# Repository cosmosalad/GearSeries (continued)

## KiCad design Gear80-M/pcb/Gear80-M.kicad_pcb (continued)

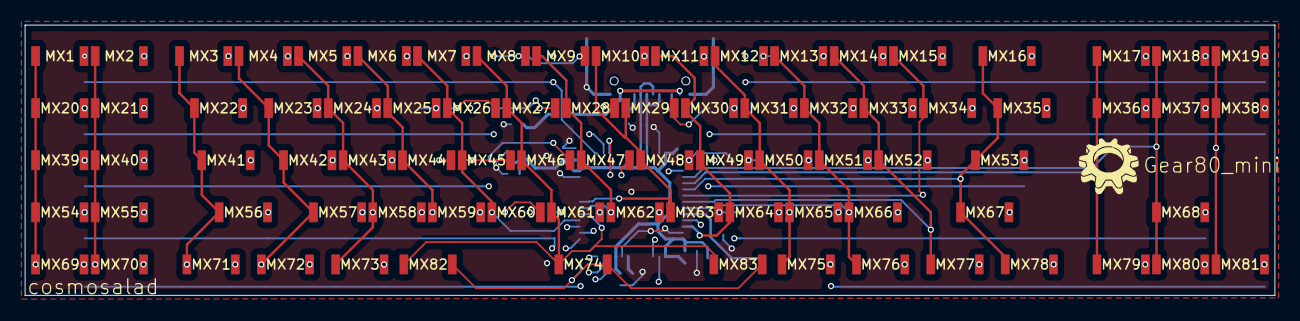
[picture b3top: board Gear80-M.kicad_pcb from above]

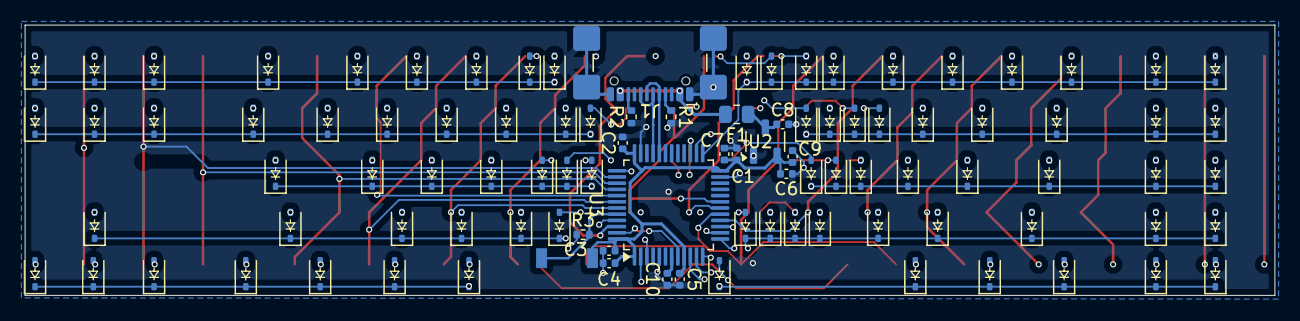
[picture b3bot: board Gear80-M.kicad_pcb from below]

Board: 4 copper layers, 100.8 x 21.8 mm, 182 parts (99 on the bottom side), 115 nets.

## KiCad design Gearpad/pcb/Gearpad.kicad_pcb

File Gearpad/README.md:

[자작 과정(kr)](https://blog.naver.com/cosmosalad/223262540878)<br/><br/>

# Gearpad<br/>
Gearpad is a 20% korean(천지인) numberpad keyboard based on the rp2040.

[천지인 연습 사이트](https://cosmosalad.github.io/onekeytype/gearpad)

<br/>

- gearpad

<br/><br/>

<p align="center">
  
</p>

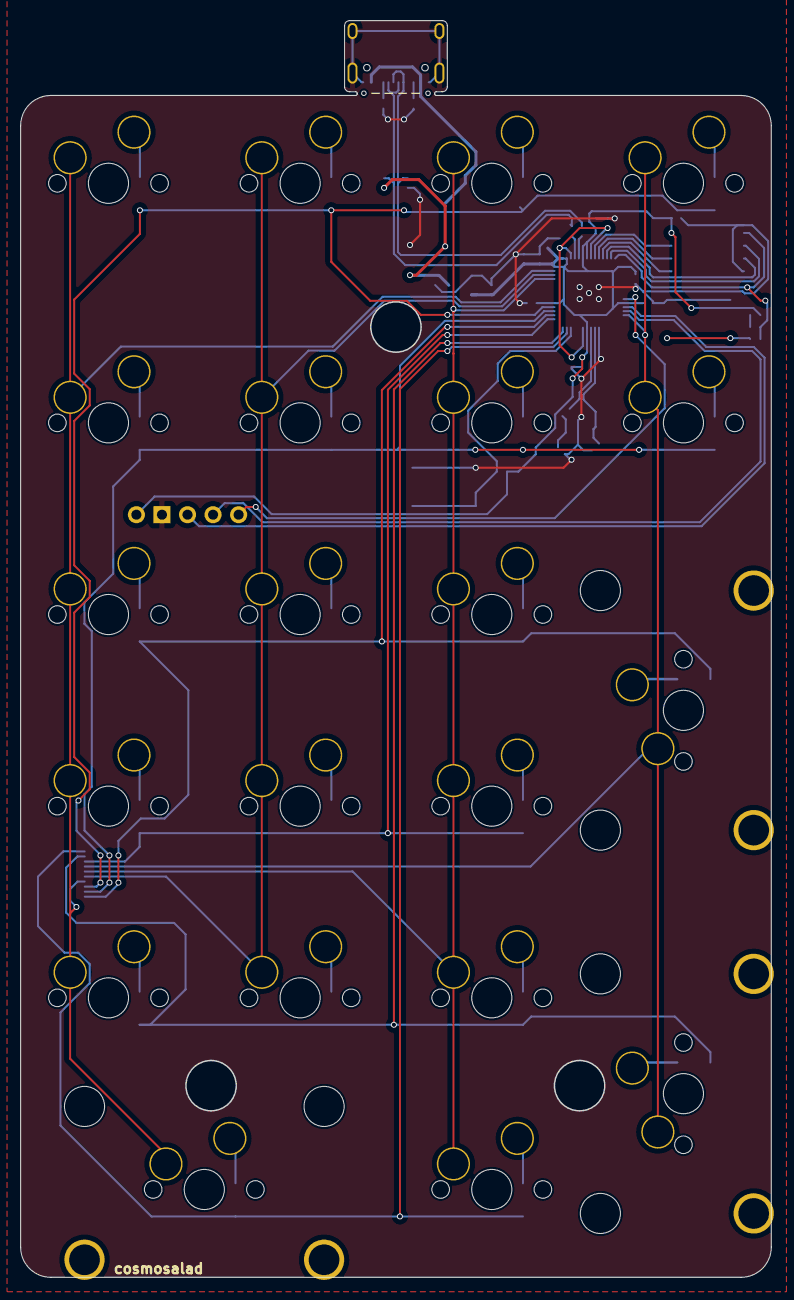
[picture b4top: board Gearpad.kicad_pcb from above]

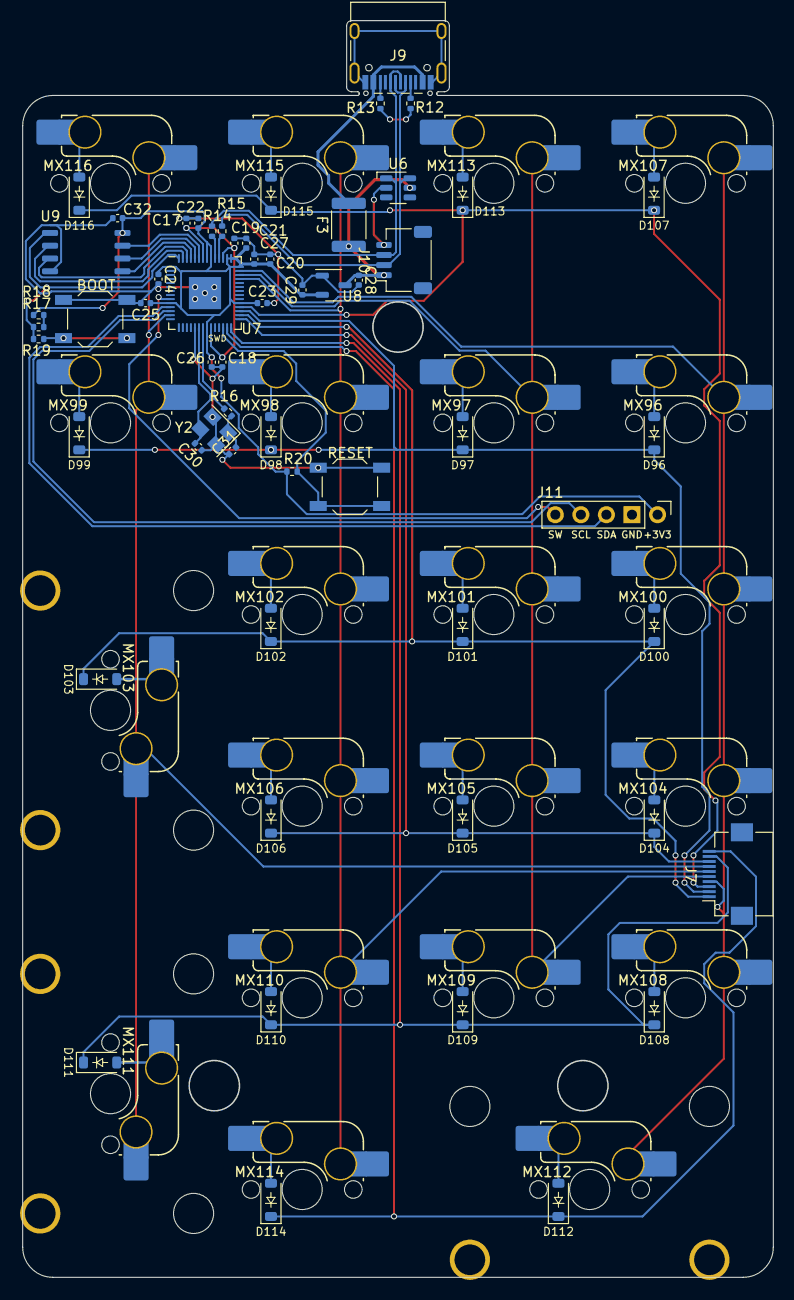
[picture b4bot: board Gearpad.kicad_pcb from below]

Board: 2 copper layers, 74.6 x 124.9 mm, 82 parts (78 on the bottom side), 57 nets.

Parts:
BOOT2: SW_Push; SW_SPST_TL3342
C17, C18, C20, C21, C22, C23, C24, C25, C26: 100n; C_0402_1005Metric
C19, C27, C28, C29, C32: 1u; C_0402_1005Metric
C30, C31: 22p; C_0402_1005Metric
D96, D97, D98, D99, D100, D101, D102, D103, D104, D105, D106, D107, D108, D109, D110, D111, D112, D113, D114, D115, D116: D_Small; D_SOD-123_new
F3: MF-MSMF050-2; Fuse_1812_4532Metric
J7: Conn_01x10_Pin; Hirose_FH12-10S-0.5SH_1x10-1MP_P0.50mm_Horizontal
J9: TYPE-C-31-M-12; USB_C_Receptacle_HRO_TYPE-C-31-M-12
J10: Conn_01x04; JST_SH_SM04B-SRSS-TB_1x04-1MP_P1.00mm_Horizontal
J11: Conn_01x05; PinSocket_1x05_P2.54mm_Vertical
MX96, MX97, MX98, MX99, MX100, MX101, MX102, MX103, MX104, MX105, MX106, MX107, MX108, MX109, MX110, MX111, MX112, MX113, MX114, MX115, MX116: MX_SW_HS; SW_MX_HS_1u
R12, R13, R17, R18, R20: 5.1k; R_0402_1005Metric
R14, R15: 27; R_0402_1005Metric
R16, R19: 1k; R_0402_1005Metric
RESET2: SW_Push; SW_SPST_TL3342
S2, S8, S9: stb; STAB_MX_P_2u
U6: SRV05-4; SOT-23-6-routable
U7: RP2040; QFN-56-1EP_7x7mm_P0.4mm_EP3.2x3.2mm
U8: XC6206P332MR; SOT-23-3
U9: W25Q128JVSIQ; SOIC-8_5.23x5.23mm_P1.27mm
Y2: X322512MSB4SI; Crystal_SMD_3225-4Pin_3.2x2.5mm

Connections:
+1V1R: C17.1, C18.1, C19.1, U7.23 (DVDD), U7.45 (VREG_VOUT), U7.50 (DVDD)
+3V3R: C20.1, C21.1, C22.1, C23.1, C24.1, C25.1, C26.1, C27.1, C29.1, C32.1, J11.1, R17.2, R20.2, U7.1 (IOVDD), U7.10 (IOVDD), U7.22 (IOVDD), U7.33 (IOVDD), U7.42 (IOVDD), U7.43 (ADC_AVDD), U7.44 (VREG_IN), U7.48 (USB_VDD), U7.49 (IOVDD), U8.2 (VO), U9.8 (VCC)
+5VR: C28.1, F3.1, J10.1, U6.5 (VP), U8.3 (VI)
COL17_N: J7.4, MX96.1, MX100.1, MX104.1, MX107.1, MX108.1, MX112.1, U7.41 (GPIO29_ADC3)
COL18_N: J7.5, MX97.1, MX101.1, MX105.1, MX109.1, MX113.1, U7.40 (GPIO28_ADC2)
COL19_N: J7.6, MX98.1, MX102.1, MX106.1, MX110.1, MX114.1, MX115.1, U7.39 (GPIO27_ADC1)
COL20_N: J7.7, MX99.1, MX103.1, MX111.1, MX116.1, U7.13 (GPIO10)
GNDR: BOOT2.1, C17.2, C18.2, C19.2, C20.2, C21.2, C22.2, C23.2, C24.2, C25.2, C26.2, C27.2, C28.2, C29.2, C30.1, C31.1, C32.2, J9.A1 (GND), J9.A12 (GND), J9.B1 (GND), J9.B12 (GND), J9.S1 (SHIELD), J10.4, J11.2, R12.2, R13.2, RESET2.1, U6.2 (VN), U7.19 (TESTEN), U7.57 (GND), U8.1 (GND), U9.4 (GND), Y2.2, Y2.4
GP_SCL_N: J11.4, U7.12 (GPIO9)
GP_SDA_N: J11.3, U7.11 (GPIO8)
unnamed: BOOT2.2, R19.1
unnamed: C31.2, R16.1, Y2.1
unnamed: D96.2 (A), MX96.2
unnamed: D97.2 (A), MX97.2
unnamed: D98.2 (A), MX98.2
unnamed: D99.2 (A), MX99.2
unnamed: D100.2 (A), MX100.2
unnamed: D101.2 (A), MX101.2
unnamed: D102.2 (A), MX102.2
unnamed: D103.2 (A), MX103.2
unnamed: D104.2 (A), MX104.2
unnamed: D105.2 (A), MX105.2
unnamed: D106.2 (A), MX106.2
unnamed: D107.2 (A), MX107.2
unnamed: D108.2 (A), MX108.2
unnamed: D109.2 (A), MX109.2
unnamed: D110.2 (A), MX110.2
unnamed: D111.2 (A), MX111.2
unnamed: D112.2 (A), MX112.2
unnamed: D113.2 (A), MX113.2
unnamed: D114.2 (A), MX114.2
unnamed: D115.2 (A), MX115.2
unnamed: D116.2 (A), MX116.2
unnamed: J9.A5 (CC1), R12.1
unnamed: J9.B5 (CC2), R13.1
unnamed: R17.1, R18.2
unnamed: R15.2, U7.46 (USB_DM)
unnamed: R14.2, U7.47 (USB_DP)
QSPI_SCLK_R: U7.52 (QSPI_SCLK), U9.6 (CLK)
QSPI_SD0_R: U7.53 (QSPI_SD0), U9.5 (DI(IO0))
QSPI_SD1_R: U7.55 (QSPI_SD1), U9.2 (DO(IO1))
QSPI_SD2_R: U7.54 (QSPI_SD2), U9.3 (IO2)
QSPI_SD3_R: U7.51 (QSPI_SD3), U9.7 (IO3)
QSPI_SS_R: R18.1, R19.2, U7.56 (QSPI_SS), U9.1 (~CS)
RESET_R: R20.1, RESET2.2, U7.26 (RUN)
ROW0_N: D107.1 (K), D113.1 (K), D115.1 (K), D116.1 (K), J7.3, U7.32 (GPIO21)
ROW1_N: D96.1 (K), D97.1 (K), D98.1 (K), D99.1 (K), J7.2, U7.31 (GPIO20)
ROW2_N: D100.1 (K), D101.1 (K), D102.1 (K), D103.1 (K), J7.1, U7.30 (GPIO19)
ROW3_N: D104.1 (K), D105.1 (K), D106.1 (K), J7.8, U7.29 (GPIO18)
ROW4_N: D108.1 (K), D109.1 (K), D110.1 (K), D111.1 (K), J7.9, U7.28 (GPIO17)
ROW5_N: D112.1 (K), D114.1 (K), J7.10, U7.27 (GPIO16)
SW_N: J11.5, U7.9 (GPIO7)
USB_D+_R: J9.A6 (D+), J9.B6 (D+), J10.3, R14.1, U6.1 (IO1)
USB_D-_R: J9.A7 (D-), J9.B7 (D-), J10.2, R15.1, U6.6 (IO4)
VBUSR: F3.2, J9.A4 (VBUS), J9.A9 (VBUS), J9.B4 (VBUS), J9.B9 (VBUS)
XIN_R: C30.2, U7.20 (XIN), Y2.3
XOUT_R: R16.2, U7.21 (XOUT)
